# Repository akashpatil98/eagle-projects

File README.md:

# eagle-projects
 This repository contains all of my Eagle CAD PCB design projects.
# Pico
The Gerber files and BoM for Pico can be found [here](https://github.com/akashpatil98/eagle-projects/tree/main/Pico).
Pico is based on Atmel ATSAMD21 microcontroller. It can be programmed using Adruino IDE or Adafruit's CircuitPython.
It has an ARM Cortex M0+ core with a maximum clock speed of 48 MHz.

# Raven BLE
Raven BLE board is based on Nordic Semiconductor's nRF52840 SoC and supports BLE 5.0. It has an ARM Cortex M4F core and supports upto 64 MHz clock speed.
The gerber files for Ravel BLE can be found [here](https://github.com/akashpatil98/eagle-projects/tree/main/Raven_BLE).

# Software
The PCBs listed here are designed using AutoDesk EAGLE software (version 9.5.2).

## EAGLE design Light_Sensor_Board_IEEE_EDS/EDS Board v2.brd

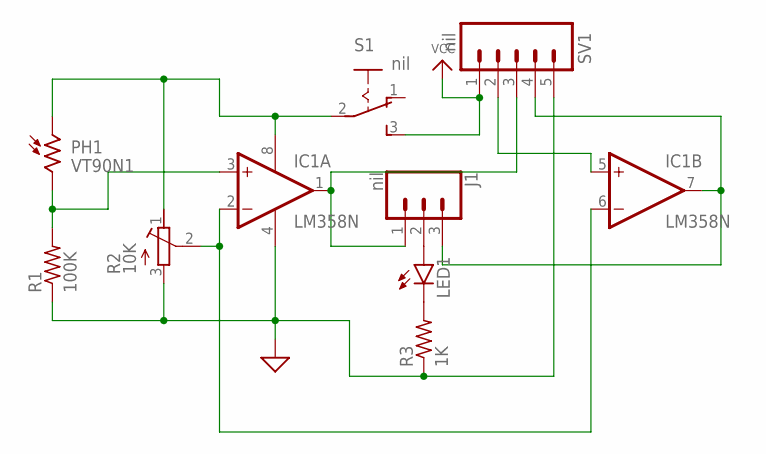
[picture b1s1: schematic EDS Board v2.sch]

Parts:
IC1: LM358N; DIL08
J1: nil; 1X03
LED1: RED; LED5MM
PH1: VT90N1; VT900
R1: 100K; 0207/7
R2: 10K; RTRIMT93YA
R3: 1K; 0207/7
S1: nil; 255SB
SV1: nil; 1X05

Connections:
GND: IC1.4 (V-), R1.1, R2.3 (A), R3.1, SV1.5
unnamed: IC1.2 (-IN), IC1.6 (-IN), R2.2 (S)
unnamed: IC1.3 (+IN), PH1.2, R1.2
unnamed: IC1.1 (OUT), J1.1, SV1.3
unnamed: LED1.K (C), R3.2
unnamed: IC1.7 (OUT), J1.3, SV1.4
unnamed: IC1.5 (+IN), SV1.2
unnamed: IC1.8 (V+), PH1.1, R2.1 (E), S1.2
unnamed: J1.2, LED1.A
VCC: S1.3 (S), SV1.1

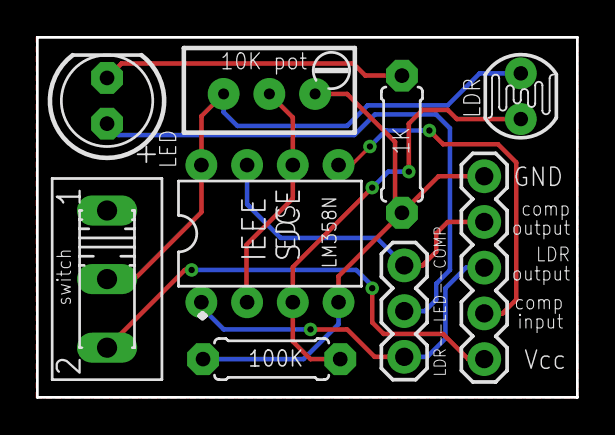
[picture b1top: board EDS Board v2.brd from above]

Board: 2 copper layers, 30.0 x 20.0 mm, 9 parts (0 on the bottom side), 10 nets.

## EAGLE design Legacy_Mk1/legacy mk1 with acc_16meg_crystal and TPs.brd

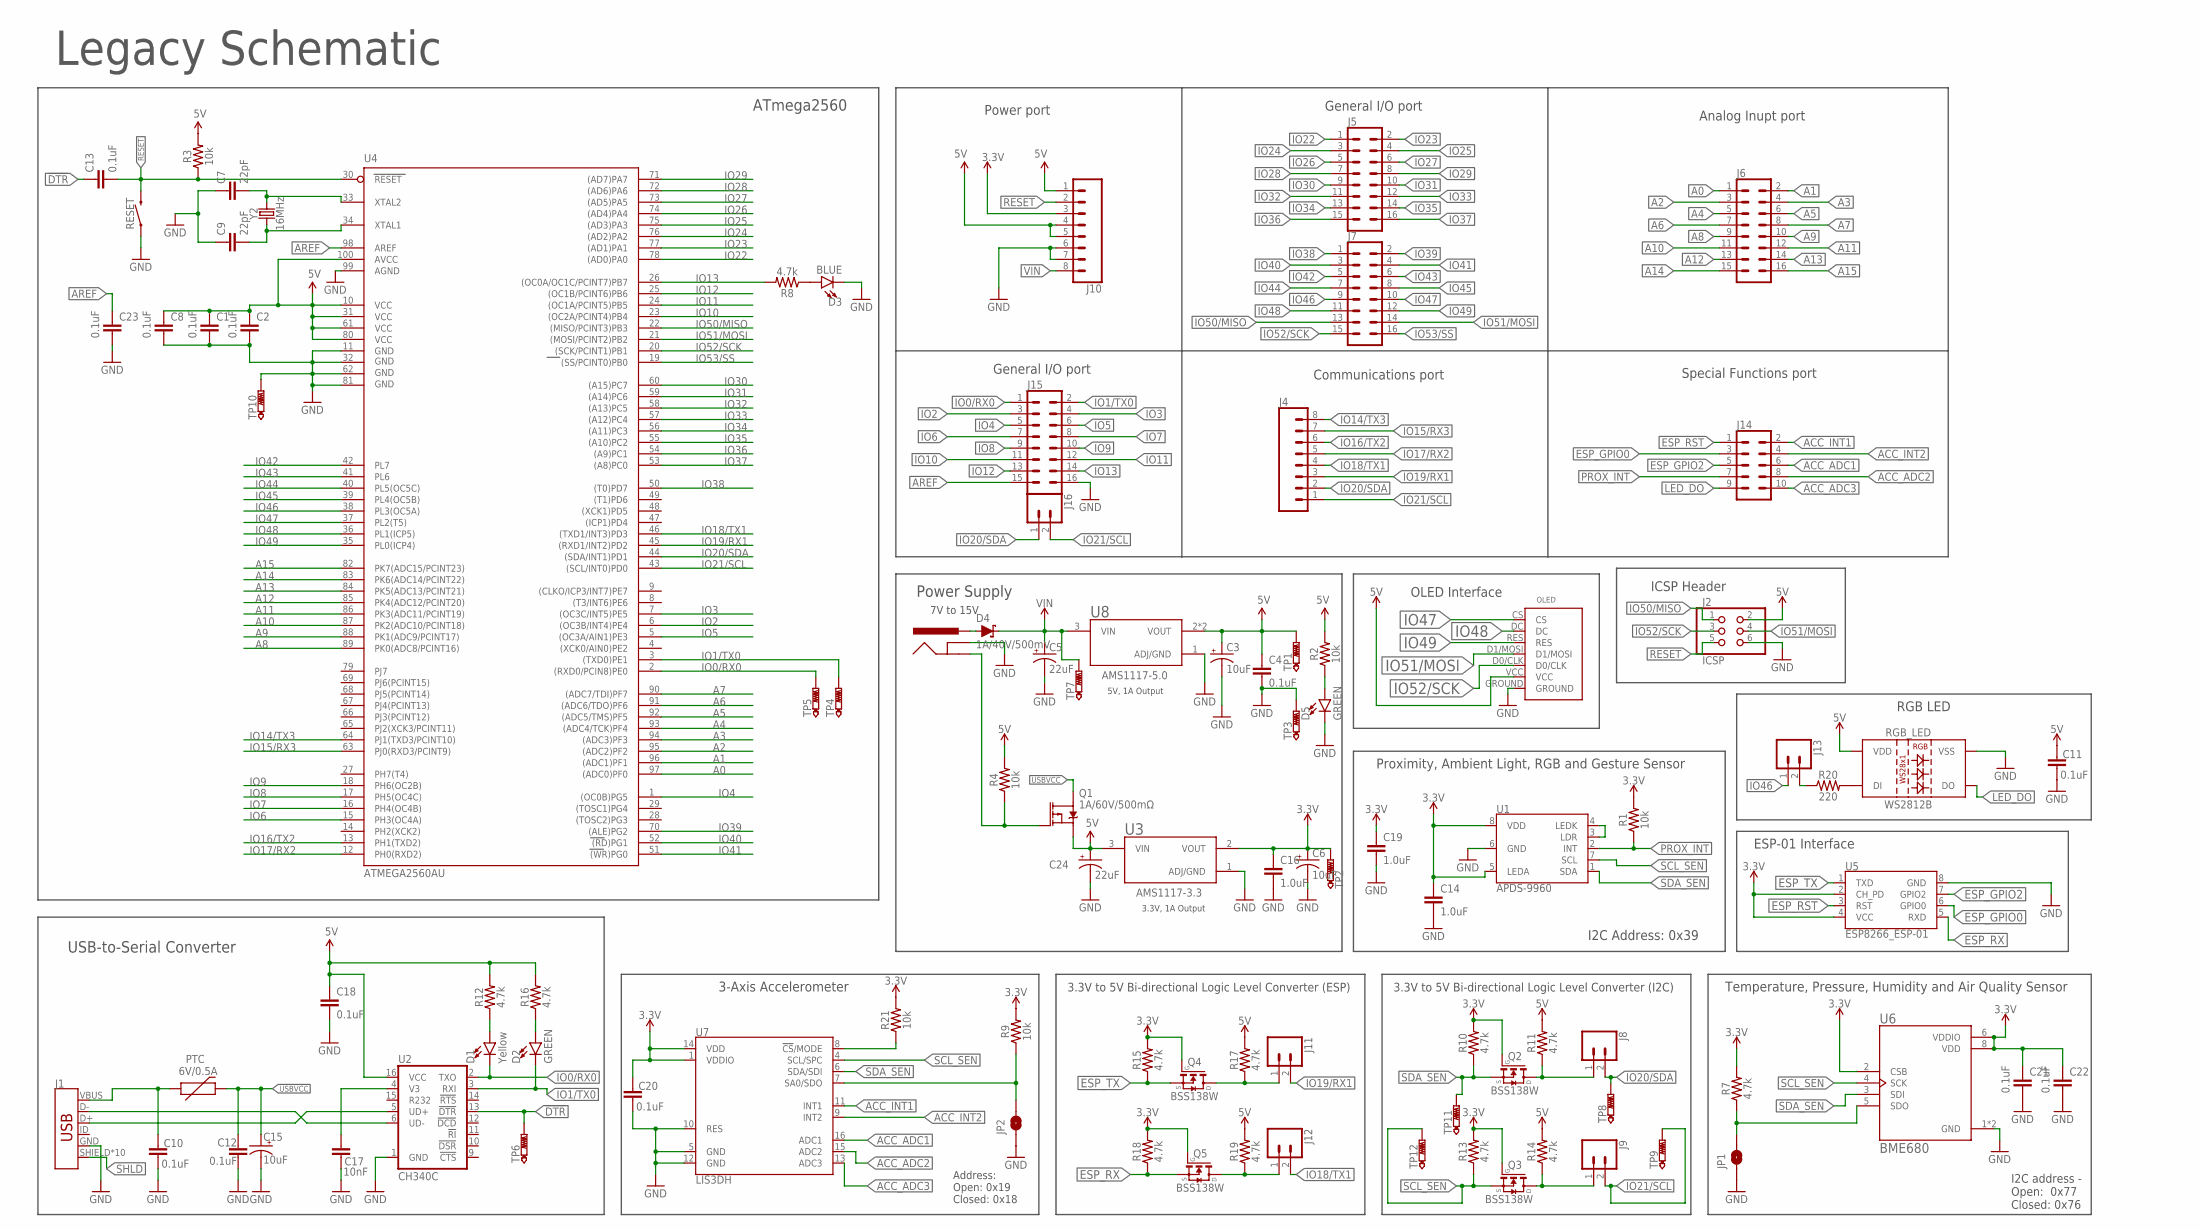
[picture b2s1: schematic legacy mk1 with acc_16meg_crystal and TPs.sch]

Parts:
C1, C2, C4, C8, C10, C11, C12, C13, C18, C20, C21, C22, C23: 0.1uF; 0603
C3, C6, C15: 10uF; EIA3216
C5, C24: 22uF; CT3528
C7, C9: 22pF; 0603
C14, C16, C19: 1.0uF; 0603-CAP
C17: 10nF; 0603-CAP
D1: Yellow; LED-0603
D2, D5: GREEN; LED-0603
D3: BLUE; LED-0603
D4: 1A/40V/500mV; SMA-DIODE
J1: AMP FCI 10103594-0001LF; USB-MICROB-PTH-MILL
J2: ICSP; 2X03
J3: POWER_JACKSLT; POWER_JACK_SLOT
J4, J10: CONN_08"; 1X08
J5, J6, J7, J15: CONN_08X2_HEADER; 2X8
J8, J9, J11, J12, J13, J16: CONN_02; 1X02
J14: CONN_05X2PTH; 2X5
JP1, JP2: JUMPER-SMT_2_NO_SILK; SMT-JUMPER_2_NO_SILK
OLED: OLED_SHIELD
PTC: 6V/0.5A; 1206
Q1: 1A/60V/500mΩ; SOT23-3
Q2, Q3, Q4, Q5: BSS138W; SOT323-R
R1, R2, R3, R4, R9, R21: 10k; 0603
R7, R8, R10, R11, R12, R13, R14, R15, R16, R17, R18, R19: 4.7k; 0603
R20: 220; 0603
RESET: MOMENTARY-SWITCH-SPST-PTH-6.0MM; TACTILE_SWITCH_PTH_6.0MM
RGB_LED: WS2812B
TP1, TP2, TP3, TP4, TP5, TP6, TP7, TP8, TP9, TP10, TP11, TP12: PTR1B1,27; B1,27
U1: APDS-9960
U2: CH340C; SO016
U3: AMS1117-3.3; SOT229P700X180-4N
U4: ATMEGA2560AU; TQFP100
U5: ESP8266_ESP-01
U6: BME680; PSON80P300X300X100-8N
U7: LIS3DH; LGA-16-3X3
U8: AMS1117-5.0; SOT229P700X180-4N
Y2: 16MHz; HC49US

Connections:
3.3V: C6.+, C14.1, C16.1, C19.1, C20.1, C21.1, C22.1, J10.3, Q2.1 (G), Q3.1 (G), Q4.1 (G), Q5.1 (G), R1.2, R7.2, R9.2, R10.2, R13.2, R15.2, R18.2, R21.2, TP2.TP, U1.5 (LEDA), U1.8 (VDD), U3.2 (VOUT), U5.2 (CH_PD), U5.4 (VCC), U6.2 (CSB), U6.6 (VDDIO), U6.8 (VDD), U7.1 (VDDIO), U7.14 (VDD)
5V: C1.1, C2.1, C3.+, C4.1, C8.1, C11.1, C18.1, C24.+, J2.2, J10.1, J10.4, J10.5, OLED.VCC, Q1.2 (S), R2.2, R3.2, R4.2, R11.2, R12.2, R14.2, R16.2, R17.2, R19.2, RGB_LED.1 (VDD), TP1.TP, U2.16 (VCC), U3.3 (VIN), U4.10 (VCC), U4.31 (VCC1), U4.61 (VCC2), U4.80 (VCC3), U4.100 (AVCC), U8.2 (VOUT), U8.4 (VOUT)
!DTR: C13.1, TP6.TP, U2.13 (!DTR)
A0: J6.1, U4.97 ((ADC0)PF0)
A1: J6.2, U4.96 ((ADC1)PF1)
A2: J6.3, U4.95 ((ADC2)PF2)
A3: J6.4, U4.94 ((ADC3)PF3)
A4: J6.5, U4.93 ((ADC4/TCK)PF4)
A5: J6.6, U4.92 ((ADC5/TMS)PF5)
A6: J6.7, U4.91 ((ADC6/TDO)PF6)
A7: J6.8, U4.90 ((ADC7/TDI)PF7)
A8: J6.9, U4.89 (PK0(ADC8/PCINT16))
A9: J6.10, U4.88 (PK1(ADC9/PCINT17))
A10: J6.11, U4.87 (PK2(ADC10/PCINT18))
A11: J6.12, U4.86 (PK3(ADC11/PCINT19))
A12: J6.13, U4.85 (PK4(ADC12/PCINT20))
A13: J6.14, U4.84 (PK5(ADC13/PCINT21))
A14: J6.15, U4.83 (PK6(ADC14/PCINT22))
A15: J6.16, U4.82 (PK7(ADC15/PCINT23))
ACC_ADC1: J14.6, U7.16 (ADC1)
ACC_ADC2: J14.8, U7.15 (ADC2)
ACC_ADC3: J14.10, U7.13 (ADC3)
ACC_INT1: J14.2, U7.11 (INT1)
ACC_INT2: J14.4, U7.9 (INT2)
AREF: C23.1, J15.15, U4.98 (AREF)
ESP_GPIO0: J14.3, U5.6 (GPIO0)
ESP_GPIO2: J14.5, U5.7 (GPIO2)
ESP_RST: J14.1, U5.3 (RST)
ESP_RX: Q5.2 (S), R18.1, U5.5 (RXD)
ESP_TX: Q4.2 (S), R15.1, U5.1 (TXD)
GND: C1.2, C2.2, C3.-, C4.2, C5.-, C6.-, C7.1, C8.2, C9.1, C10.2, C11.2, C12.2, C14.2, C15.-, C16.2, C17.2, C18.2, C19.2, C20.2, C21.2, C22.2, C23.2, C24.-, D3.C, D5.C, J1.GND, J2.6, J3.GND@1 (GNDBREAK), J10.6, J10.7, J15.16, JP1.1, JP2.1, OLED.GROUND, RESET.1, RGB_LED.3 (VSS), TP3.TP, TP10.TP, U1.6 (GND), U2.1 (GND), U3.1 (ADJ/GND), U4.11 (GND), U4.32 (GND1), U4.62 (GND2), U4.81 (GND3), U4.99 (AGND), U5.8 (GND), U6.1 (GND), U6.7 (GND), U7.5 (GND), U7.10 (RES), U7.12 (GND), U8.1 (ADJ/GND)
INSERT: J3.GND@2 (GND), Q1.1 (G), R4.1
IO0/RX0: D1.C, J15.1, TP5.TP, U2.2 (TXO), U4.2 ((RXD0/PCIN8)PE0)
IO1/TX0: D2.C, J15.2, TP4.TP, U2.3 (RXI), U4.3 ((TXD0)PE1)
IO2: J15.3, U4.6 ((OC3B/INT4)PE4)
IO3: J15.4, U4.7 ((OC3C/INT5)PE5)
IO4: J15.5, U4.1 ((OC0B)PG5)
IO5: J15.6, U4.5 ((OC3A/AIN1)PE3)
IO6: J15.7, U4.15 (PH3(OC4A))
IO7: J15.8, U4.16 (PH4(OC4B))
IO8: J15.9, U4.17 (PH5(OC4C))
IO9: J15.10, U4.18 (PH6(OC2B))
IO10: J15.11, U4.23 ((OC2A/PCINT4)PB4)
IO11: J15.12, U4.24 ((OC1A/PCINT5)PB5)
IO12: J15.13, U4.25 ((OC1B/PCINT6)PB6)
IO13: J15.14, R8.2, U4.26 ((OC0A/OC1C/PCINT7)PB7)
IO14/TX3: J4.8, U4.64 (PJ1(TXD3/PCINT10))
IO15/RX3: J4.7, U4.63 (PJ0(RXD3/PCINT9))
IO16/TX2: J4.6, U4.13 (PH1(TXD2))
IO17/RX2: J4.5, U4.12 (PH0(RXD2))
IO18/TX1: J4.4, J12.2, U4.46 ((TXD1/INT3)PD3)
IO19/RX1: J4.3, J11.2, U4.45 ((RXD1/INT2)PD2)
IO20/SDA: J4.2, J8.2, J16.1, TP8.TP, U4.44 ((SDA/INT1)PD1)
IO21/SCL: J4.1, J9.2, J16.2, TP9.TP, U4.43 ((SCL/INT0)PD0)
IO22: J5.1, U4.78 ((AD0)PA0)
IO23: J5.2, U4.77 ((AD1)PA1)
IO24: J5.3, U4.76 ((AD2)PA2)
IO25: J5.4, U4.75 ((AD3)PA3)
IO26: J5.5, U4.74 ((AD4)PA4)
IO27: J5.6, U4.73 ((AD5)PA5)
IO28: J5.7, U4.72 ((AD6)PA6)
IO29: J5.8, U4.71 ((AD7)PA7)
IO30: J5.9, U4.60 ((A15)PC7)
IO31: J5.10, U4.59 ((A14)PC6)
IO32: J5.11, U4.58 ((A13)PC5)
IO33: J5.12, U4.57 ((A12)PC4)
IO34: J5.13, U4.56 ((A11)PC3)
IO35: J5.14, U4.55 ((A10)PC2)
IO36: J5.15, U4.54 ((A9)PC1)
IO37: J5.16, U4.53 ((A8)PC0)
IO38: J7.1, U4.50 ((T0)PD7)
IO39: J7.2, U4.70 ((ALE)PG2)
IO40: J7.3, U4.52 ((RD)PG1)
IO41: J7.4, U4.51 ((WR)PG0)
IO42: J7.5, U4.42 (PL7)
IO43: J7.6, U4.41 (PL6)
IO44: J7.7, U4.40 (PL5(OC5C))
IO45: J7.8, U4.39 (PL4(OC5B))
IO46: J7.9, J13.1, U4.38 (PL3(OC5A))
IO47: J7.10, OLED.CS, U4.37 (PL2(T5))
IO48: J7.11, OLED.DC, U4.36 (PL1(ICP5))
IO49: J7.12, OLED.RES, U4.35 (PL0(ICP4))
IO50/MISO: J2.1, J7.13, U4.22 ((MISO/PCINT3)PB3)
IO51/MOSI: J2.4, J7.14, OLED.D1/MOSI, U4.21 ((MOSI/PCINT2)PB2)
IO52/SCK: J2.3, J7.15, OLED.D0/CLK, U4.20 ((SCK/PCINT1)PB1)
IO53/SS: J7.16, U4.19 ((SS/PCINT0)PB0)
LED_DO: J14.9, RGB_LED.2 (DO)
unnamed: C7.2, U4.33 (XTAL2), Y2.2
unnamed: D5.A, R2.1
unnamed: C9.2, U4.34 (XTAL1), Y2.1
unnamed: JP1.2, R7.1, U6.5 (SDO)
unnamed: D2.A, R16.1
unnamed: C17.1, U2.4 (V3)
unnamed: U1.3 (LDR), U1.4 (LEDK)
unnamed: D3.A, R8.1
unnamed: D1.A, R12.1
unnamed: JP2.2, R9.1, U7.7 (SA0/SDO)
unnamed: J13.2, R20.1
unnamed: J8.1, Q2.3 (D), R11.1
unnamed: J1.D-, U2.6 (UD-)
unnamed: J1.D+, U2.5 (UD+)
unnamed: J11.1, Q4.3 (D), R17.1
unnamed: J9.1, Q3.3 (D), R14.1
unnamed: R21.1, U7.8 (!CS!/MODE)
unnamed: R20.2, RGB_LED.4 (DI)
unnamed: J12.1, Q5.3 (D), R19.1
PROX_INT: J14.7, R1.1, U1.2 (INT)
PWRIN: D4.A, J3.PWR
RESET: C13.2, J2.5, J10.2, R3.1, RESET.3 (2), U4.30 (RESET)
SCL_SEN: Q3.2 (S), R13.1, TP12.TP, U1.7 (SCL), U6.4 (SCK), U7.4 (SCL/SPC)
SDA_SEN: Q2.2 (S), R10.1, TP11.TP, U1.1 (SDA), U6.3 (SDI), U7.6 (SDA/SDI)
SHLD: J1.SHIELD, J1.SHIELD2 (SHIELD), J1.SHIELD3 (SHIELD), J1.SHIELD4 (SHIELD), J1.SHIELD5 (SHIELD), J1.SHIELD6 (SHIELD), J1.SHIELD7 (SHIELD), J1.SHIELD8 (SHIELD), J1.SHIELD9 (SHIELD), J1.SHIELD10 (SHIELD)
USBVCC: C12.1, C15.+, PTC.2, Q1.3 (D)
VIN: C5.+, D4.C, J10.8, TP7.TP, U8.3 (VIN)
VUSB: C10.1, J1.VBUS, PTC.1

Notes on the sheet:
USB-to-Serial Converter
Power Supply
3-Axis Accelerometer
3.3V to 5V Bi-directional Logic Level Converter (I2C)
3.3V to 5V Bi-directional Logic Level Converter (ESP)
RGB LED
Address: Open: 0x19 Closed: 0x18
7V to 15V
ESP-01 Interface
ICSP Header
Proximity, Ambient Light, RGB and Gesture Sensor
I2C Address: 0x39
Temperature, Pressure, Humidity and Air Quality Sensor
I2C address - Open: 0x77 Closed: 0x76
Power port
Communications port
Special Functions port
Analog Inupt port
General I/O port
ATmega2560
OLED Interface
Legacy Schematic
5V, 1A Output
3.3V, 1A Output

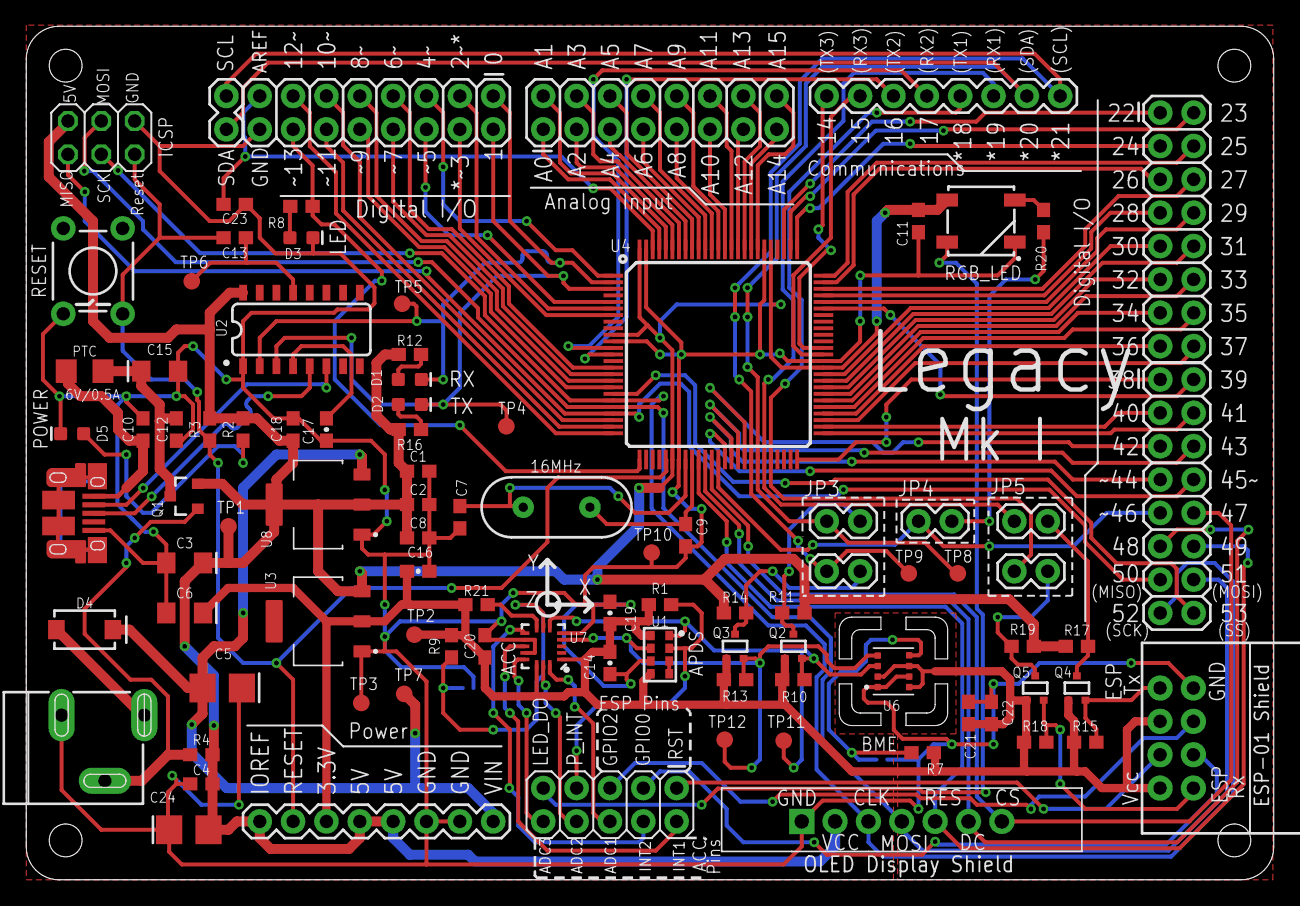
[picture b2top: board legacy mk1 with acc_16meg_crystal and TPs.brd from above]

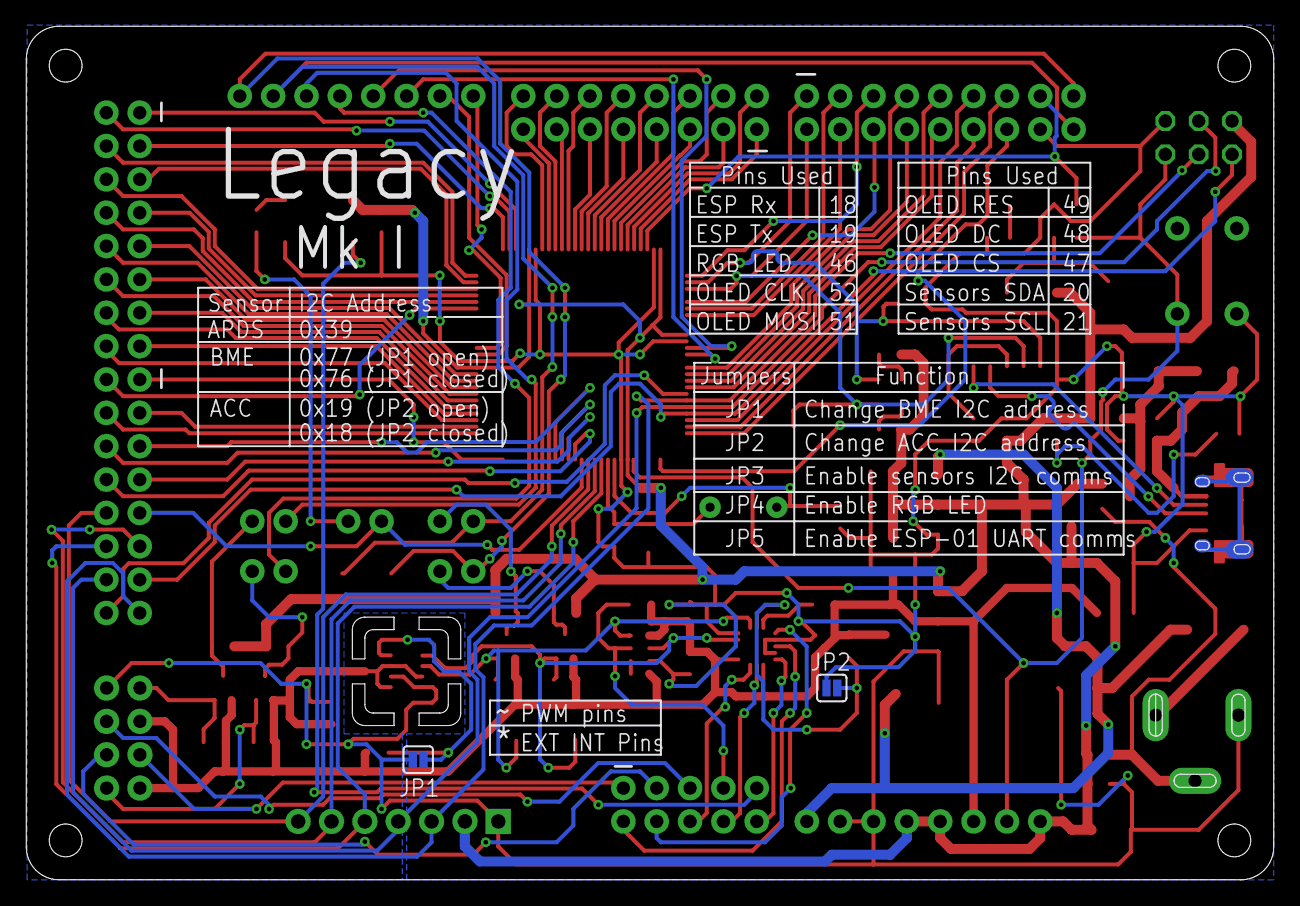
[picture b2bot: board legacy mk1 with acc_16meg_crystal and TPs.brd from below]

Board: 2 copper layers, 95.0 x 65.0 mm, 96 parts (2 on the bottom side), 115 nets.

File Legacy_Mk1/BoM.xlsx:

Qty | Value | Device | Package | Parts | Description
6 |  | CONN_02 | 1X02 | J8, J9, J11, J12, J13, J16 | Multi connection point. Often used as Generic Header-pin footprint for 0.1 inch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
1 |  | CONN_05X2PTH | 2X5 | J14 | Multi connection point. Often used as Generic Header-pin footprint for 0.1 inch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
2 |  | CONN_08";1X08" | J4, J10 | J4, J10 | Multi connection point. Often used as Generic Header-pin footprint for 0.1 inch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
4 |  | CONN_08X2_HEADER | 2X8 | J5, J6, J7, J15 | Multi connection point. Often used as Generic Header-pin footprint for 0.1 inch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
13 | 0.1uF | 0.1UF-0603-25V-(+80/-20%) | 0603 | C1, C2, C4, C8, C10, C11, C12, C13, C18, C20, C21, C22, C23 | 0.1ÂµF ceramic capacitors
3 | 1.0uF | 1.0UF-16V-10%(0603) | 0603-CAP | C14, C16, C19 | CAP-00868
6 | 10k | 10KOHM-0603-1/10W-1% | 0603 | R1, R2, R3, R4, R9, R21 | 10kÎ© resistor
1 | 10nF | 10NF/10000PF-50V-10%(0603) | 0603-CAP | C17 | CAP-00867
3 | 10uF | 10UF-POLAR-EIA3216-16V-10%(TANT) | EIA3216 | C3, C6, C15 | 10.0ÂµF polarized capacitors
1 | 16MHz | CRYSTAL-16MHZPTH-HC49US | HC49US | Y2 | 16MHz Crystal
1 | 1A/40V/500mV | DIODE-SCHOTTKY-SS14 | SMA-DIODE | D4 | Schottky diode
1 | 1A/60V/500mÎ© | MOSFET-PCH-ZXMP6A13F | SOT23-3 | Q1 | P-channel MOSFETs
1 | 220 | 220OHM-0603-1/10W-1% | 0603 | R20 | 220Î© resistor
2 | 22pF | 22PF-0603-50V-5% | 0603 | C7, C9 | 22pF ceramic capacitors
2 | 22uF | CPOL-USCT3528 | CT3528 | C5, C24 | POLARIZED CAPACITOR, American symbol
12 | 4.7k | 4.7KOHM-0603-1/10W-1% | 0603 | R7, R8, R10, R11, R12, R13, R14, R15, R16, R17, R18, R19 | 4.7kÎ© resistor
1 | 6V/0.5A | PPTC_6V500MA-2 | 1206 | PTC | Resettable Fuse PPTC
1 | AMP FCI 10103594-0001LF | USB_MICRO-B_HALF_PTH_MILL | USB-MICROB-PTH-MILL | J1 | USB Type Micro-B Connector
1 | AMS1117-3.3 | AMS1117-3.3 | SOT229P700X180-4N | U3 | Sot223/Pkg 1-Amp 3.3-Volt Low Drop Out Voltage Regulatator
1 | AMS1117-5.0 | AMS1117-5.0 | SOT229P700X180-4N | U8 | Sot223/Pkg 1-Amp 5-Volt Low Drop Out Voltage Regulatator
1 | APDS-9960 | APDS-9960 | APDS-9960 | U1 | Avago APDS-9960 Digital Proximity, Ambient Light, RGB, and Gesture Sensor.
1 | ATMEGA2560AU | ATMEGA2560AU | TQFP100 | U4 | Atmel 100-pin 8-bit uC
1 | BLUE | LED-BLUE0603 | LED-0603 | D3 | Blue SMD LED
1 | BME680 | BME680 | PSON80P300X300X100-8N | U6 | Integrated Environmental Unit
4 | BSS138W | BSS138W | SOT323-R | Q2, Q3, Q4, Q5 | N-Channel MOSFET
1 | CH340C | CH340C | SO016 | U2
1 | ESP8266_ESP-01 | ESP8266_ESP-01 | ESP8266_ESP-01 | U5 | ESP8266 ESP-01 Module
2 | GREEN | LED-GREEN0603 | LED-0603 | D2, D5 | Green SMD LED
1 | ICSP | PINHD-2X3 | 2X03 | J2 | PIN HEADER
2 | JUMPER-SMT_2_NO_SILK | JUMPER-SMT_2_NO_SILK | SMT-JUMPER_2_NO_SILK | JP1, JP2 | Normally open jumper
1 | LIS3DH | LIS3DH | LGA-16-3X3 | U7 | ST Microelectronics LIS3DH 3-Axis +/-2/4/8/16g SPI/I2C Accelerometer
1 | MOMENTARY-SWITCH-SPST-PTH-6.0MM | MOMENTARY-SWITCH-SPST-PTH-6.0MM | TACTILE_SWITCH_PTH_6.0MM | RESET | Momentary Switch (Pushbutton) - SPST
1 | OLED_SHIELD | OLED_SHIELD | OLED_SHIELD | OLED | This is an OLED display shield for 0.96 OLED display module (SSD1306)."
1 | POWER_JACKSLT | POWER_JACKSLT | POWER_JACK_SLOT | J3 | Power Jack Connector
1 | WS2812B | WS2812B | WS2812B | RGB_LED | WS2812B SMD addressable RGB LED
1 | Yellow | LED-YELLOW0603 | LED-0603 | D1 | Yellow SMD LED

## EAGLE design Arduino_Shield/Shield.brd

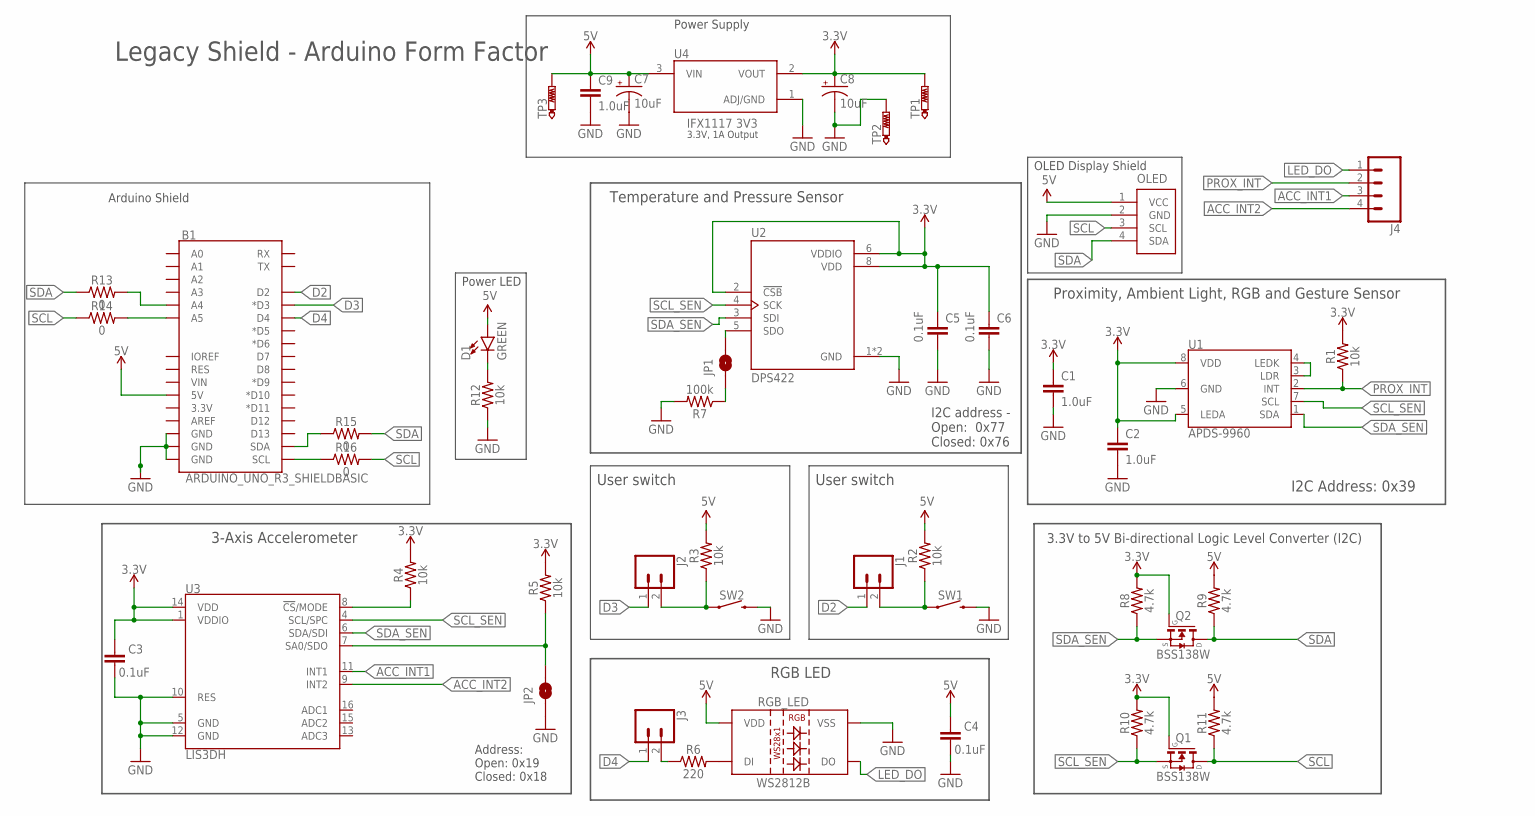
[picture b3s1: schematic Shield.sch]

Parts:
B1: ARDUINO_UNO_R3_SHIELDBASIC; UNO_R3_SHIELD
C1, C2, C9: 1.0uF; 0603-CAP
C3, C4, C5, C6: 0.1uF; 0603
C7, C8: 10uF; EIA3528
D1: GREEN; LED-1206
J1, J2, J3: CONN_02; 1X02
J4: CONN_04; 1X04
JP1, JP2: JUMPER-SMT_2_NO_SILK; SMT-JUMPER_2_NO_SILK
OLED: OLED_4_PIN; OLED_4PIN
Q1, Q2: BSS138W; SOT323-R; DIGI-KEY_PART_NUMBER BSS138WH6327XTSA1CT-ND
R1, R2, R3, R4, R5, R12: 10k; 0603
R6: 220; 0603
R7: 100k; 0603
R8, R9, R10, R11: 4.7k; 0603
R13, R14, R15, R16: 0; 0603
RGB_LED: WS2812B
SW1, SW2: MOMENTARY-SWITCH-SPST-PTH-6.0MM; TACTILE_SWITCH_PTH_6.0MM
TP1, TP2, TP3: PTR1TP08R; TP08R
U1: APDS-9960; DIGI-KEY_PART_NUMBER 516-3480-1-ND
U2: DPS422; XDCR_DPS422; DIGI-KEY_PART_NUMBER DPS422XTSA1CT-ND
U3: LIS3DH; LGA-16-3X3
U4: IFX1117 3V3; SOT229P700X180-4N; DIGI-KEY_PART_NUMBER IFX1117MEV33HTMA1CT-ND

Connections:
3.3V: C1.1, C2.1, C3.1, C5.1, C6.1, C8.A (+), Q1.1 (G), Q2.1 (G), R1.2, R4.2, R5.2, R8.2, R10.2, TP1.TP, U1.5 (LEDA), U1.8 (VDD), U2.2 (!CSB), U2.6 (VDDIO), U2.8 (VDD), U3.1 (VDDIO), U3.14 (VDD), U4.2 (VOUT)
5V: B1.5V, C4.1, C7.A (+), C9.1, D1.A, OLED.1 (VCC), R2.2, R3.2, R9.2, R11.2, RGB_LED.1 (VDD), TP3.TP, U4.3 (VIN)
ACC_INT1: J4.3, U3.11 (INT1)
ACC_INT2: J4.4, U3.9 (INT2)
D2: B1.D2, J1.1
D3: B1.D3 (*D3), J2.1
D4: B1.D4, J3.1
GND: B1.GND@0 (GND), B1.GND@1 (GND), B1.GND@2 (GND), C1.2, C2.2, C3.2, C4.2, C5.2, C6.2, C7.C (-), C8.C (-), C9.2, JP2.1, OLED.2 (GND), R7.2, R12.1, RGB_LED.3 (VSS), SW1.3 (2), SW2.3 (2), TP2.TP, U1.6 (GND), U2.1 (GND), U2.7 (GND), U3.5 (GND), U3.10 (RES), U3.12 (GND), U4.1 (ADJ/GND)
LED_DO: J4.1, RGB_LED.2 (DO)
unnamed: J1.2, R2.1, SW1.1
unnamed: J2.2, R3.1, SW2.1
unnamed: D1.C, R12.2
unnamed: JP1.2, U2.5 (SDO)
unnamed: JP1.1, R7.1
unnamed: B1.A4, R13.2
unnamed: U1.3 (LDR), U1.4 (LEDK)
unnamed: B1.A5, R14.2
unnamed: B1.SDA, R15.1
unnamed: JP2.2, R5.1, U3.7 (SA0/SDO)
unnamed: J3.2, R6.1
unnamed: B1.SCL, R16.1
unnamed: R4.1, U3.8 (!CS!/MODE)
unnamed: R6.2, RGB_LED.4 (DI)
PROX_INT: J4.2, R1.1, U1.2 (INT)
SCL: OLED.3 (SCL), Q1.3 (D), R11.1, R14.1, R16.2
SCL_SEN: Q1.2 (S), R10.1, U1.7 (SCL), U2.4 (SCK), U3.4 (SCL/SPC)
SDA: OLED.4 (SDA), Q2.3 (D), R9.1, R13.1, R15.2
SDA_SEN: Q2.2 (S), R8.1, U1.1 (SDA), U2.3 (SDI), U3.6 (SDA/SDI)

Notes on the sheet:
3-Axis Accelerometer
Address: Open: 0x19 Closed: 0x18
3.3V to 5V Bi-directional Logic Level Converter (I2C)
Temperature and Pressure Sensor
I2C address - Open: 0x77 Closed: 0x76
Proximity, Ambient Light, RGB and Gesture Sensor
I2C Address: 0x39
RGB LED
User switch
Power LED
3.3V, 1A Output
Power Supply
OLED Display Shield
Arduino Shield
Legacy Shield - Arduino Form Factor

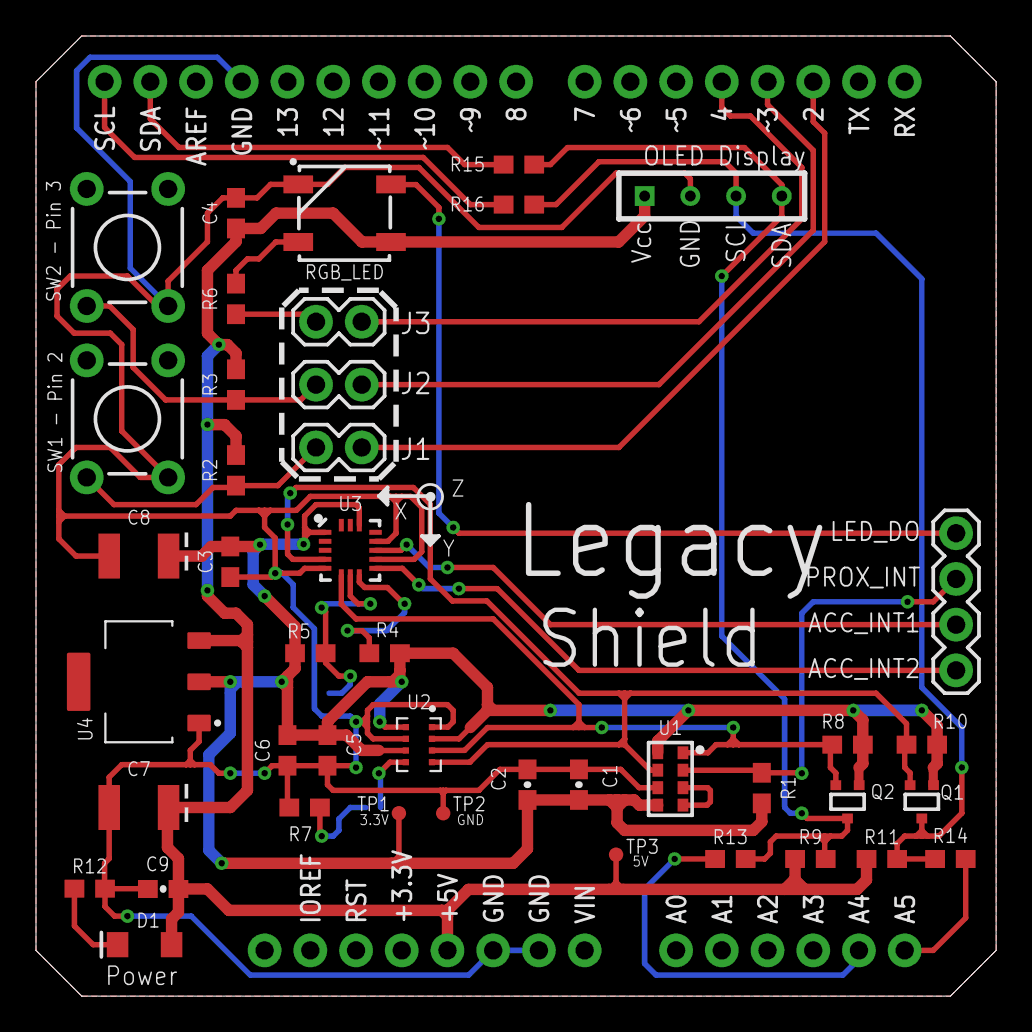
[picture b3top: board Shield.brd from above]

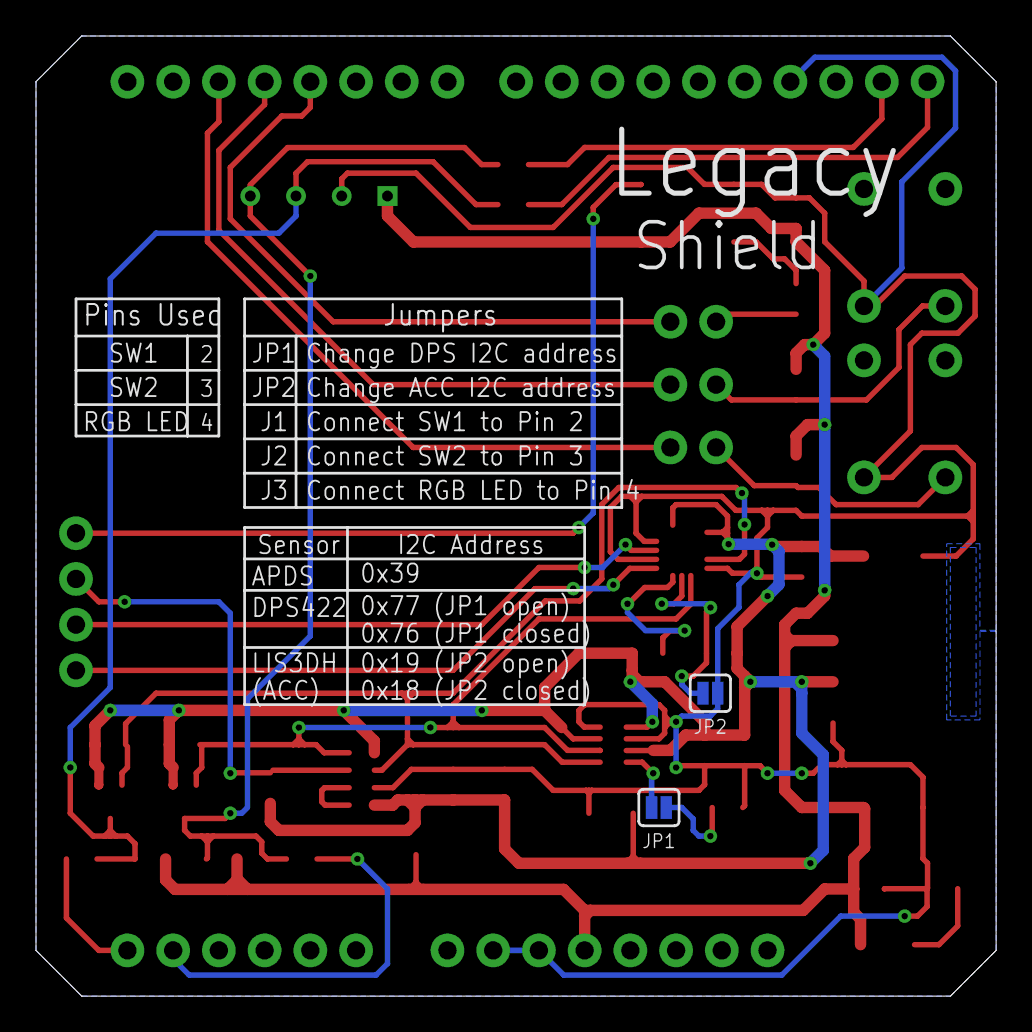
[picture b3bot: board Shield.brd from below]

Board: 2 copper layers, 53.3 x 53.3 mm, 46 parts (2 on the bottom side), 28 nets.

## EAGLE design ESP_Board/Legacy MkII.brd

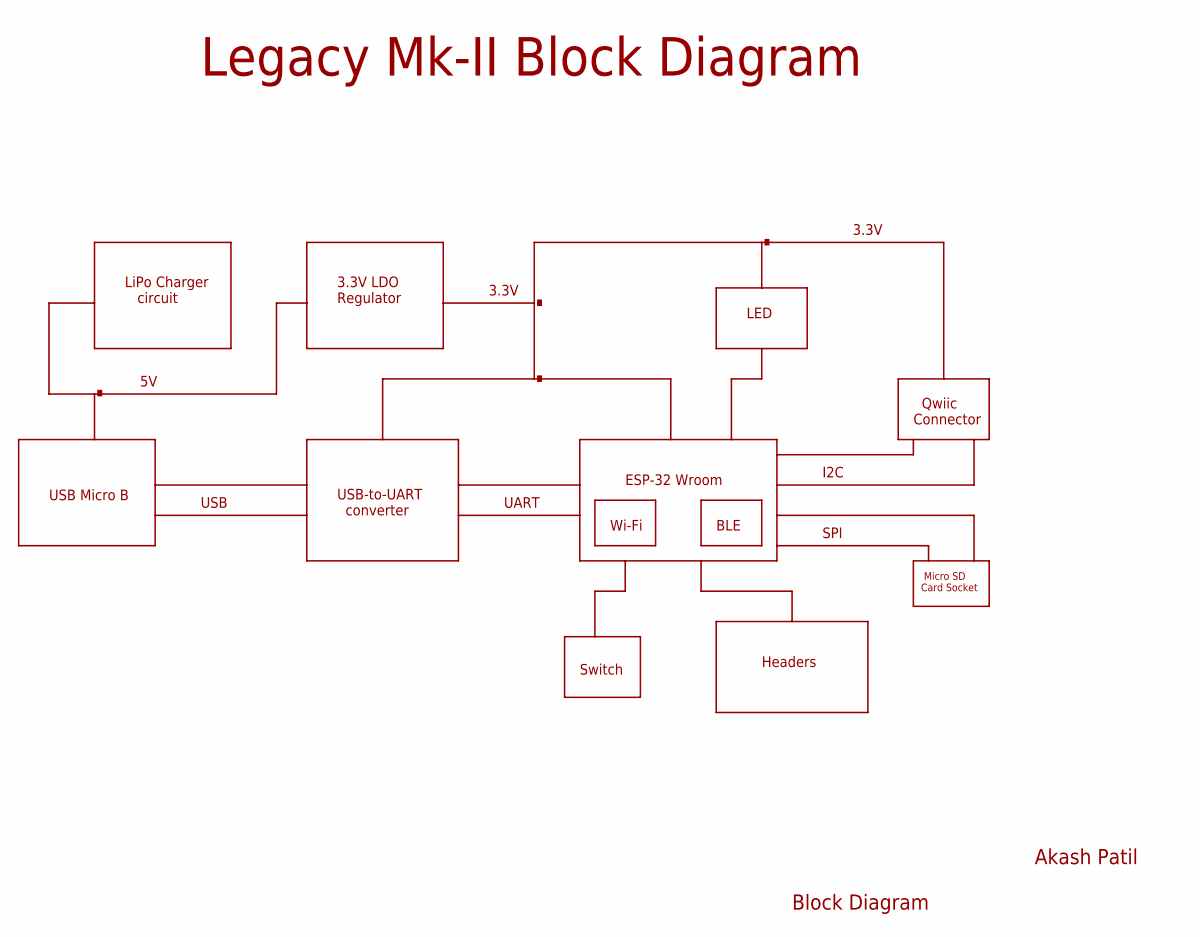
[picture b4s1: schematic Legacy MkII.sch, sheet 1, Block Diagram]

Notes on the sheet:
Akash Patil
Block Diagram
USB Micro B
USB-to-UART converter
3.3V LDO Regulator
LiPo Charger circuit
ESP-32 Wroom
Wi-Fi
BLE
LED
Switch
Qwiic Connector
3.3V
USB
UART
I2C
Headers
Legacy Mk-II Block Diagram
Micro SD Card Socket
SPI

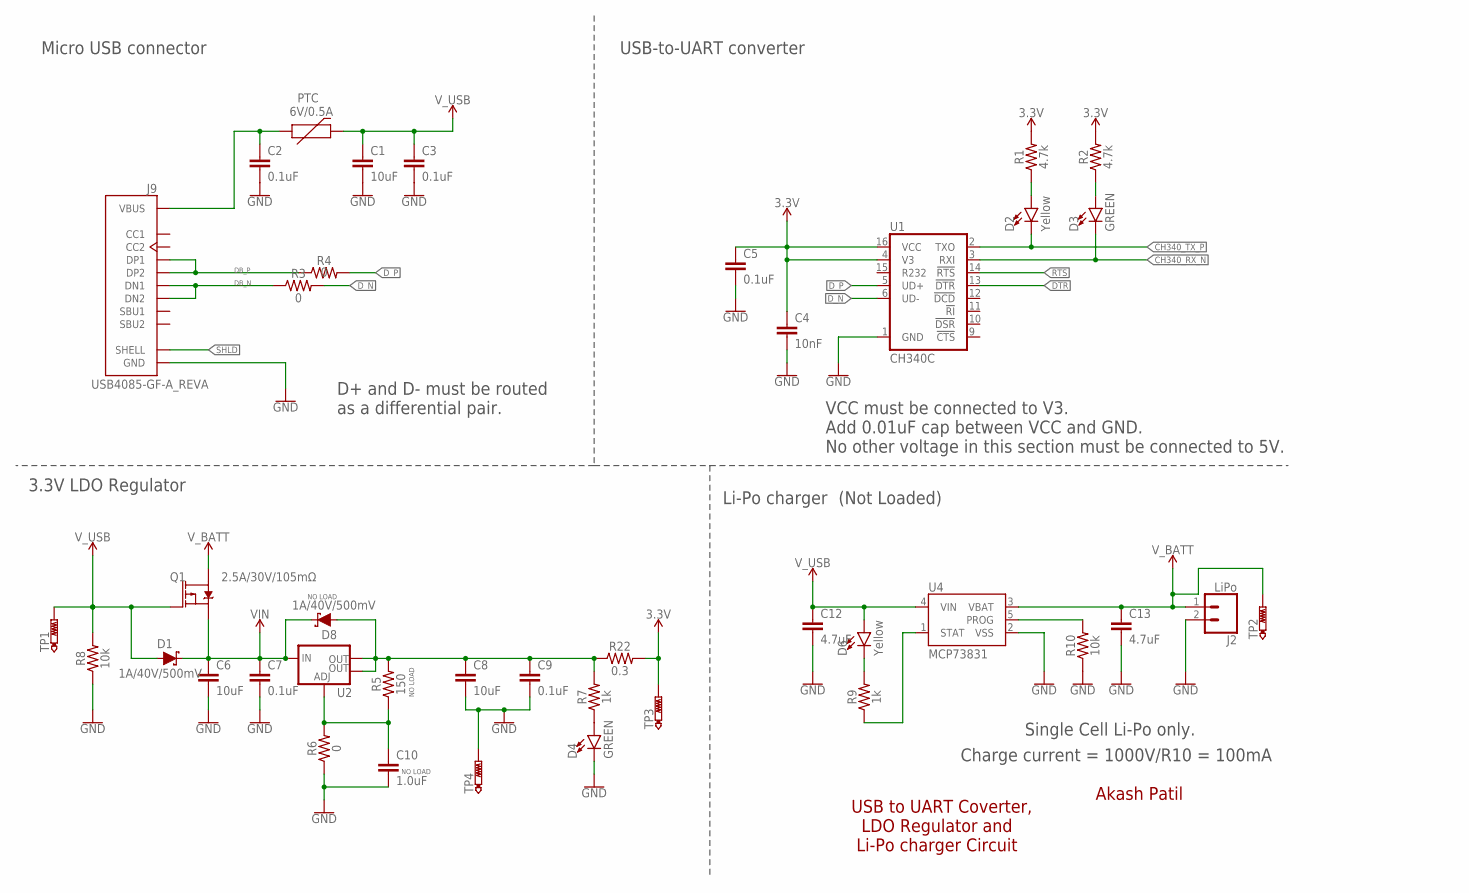
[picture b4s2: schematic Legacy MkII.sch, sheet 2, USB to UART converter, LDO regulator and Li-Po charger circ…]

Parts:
C1, C6, C8: 10uF; 1210
C2, C3, C5, C7, C9: 0.1uF; 0603
C4: 10nF; 0603
C10: 1.0uF; 0603
C12, C13: 4.7uF; 1206
D1, D8: 1A/40V/500mV; SMA-DIODE
D2, D6: Yellow; LED-0603
D3, D4: GREEN; LED-0603
J2: LiPo; JST-2-PTH-NS
J9: USB4085-GF-A_REVA; GCT_USB4085-GF-A_REVA
PTC: 6V/0.5A; 1206
Q1: 2.5A/30V/105mΩ; SOT23-3
R1, R2: 4.7k; 0603
R3, R4, R6: 0; 0603
R5: 150; 0603
R7, R9: 1k; 0603
R8, R10: 10k; 0603
R22: 0.3; 0805
TP1, TP2, TP3, TP4: PTR1B1,27; B1,27
U1: CH340C; SO016
U2: V_REG_LM1117SOT223; SOT223
U4: MCP73831; SOT23-5

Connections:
3.3V: C4.1, C5.1, R1.2, R2.2, R22.2, TP3.TP, U1.4 (V3), U1.16 (VCC); also elsewhere on the board
CH340_RX_N: D3.C, U1.3 (RXI); also elsewhere on the board
CH340_TX_P: D2.C, U1.2 (TXO); also elsewhere on the board
DB_N: J9.A7 (DN1), J9.B7 (DN2), R3.1
DB_P: J9.A6 (DP1), J9.B6 (DP2), R4.1
DTR: U1.13 (!DTR); also elsewhere on the board
D_N: R3.2, U1.6 (UD-)
D_P: R4.2, U1.5 (UD+)
GND: C1.2, C2.2, C3.2, C4.2, C5.2, C6.2, C7.2, C8.2, C9.2, C10.2, C12.2, C13.2, D4.C, J2.2, J9.A1 (GND), J9.A12 (GND), J9.B1 (GND), J9.B12 (GND), R6.1, R8.1, R10.1, TP4.TP, U1.1 (GND), U4.2 (VSS); also elsewhere on the board
unnamed: C2.1, J9.A4 (VBUS), J9.A9 (VBUS), J9.B4 (VBUS), J9.B9 (VBUS), PTC.1
unnamed: D4.A, R7.1
unnamed: C8.1, C9.1, D8.A, R5.2, R7.2, R22.1, U2.2 (OUT), U2.4 (OUT)
unnamed: D2.A, R1.1
unnamed: D3.A, R2.1
unnamed: C10.1, R5.1, R6.2, U2.1 (ADJ)
unnamed: D6.C, R9.2
unnamed: R9.1, U4.1 (STAT)
unnamed: R10.2, U4.5 (PROG)
RTS: U1.14 (!RTS); also elsewhere on the board
SHLD: J9.P1 (SHELL), J9.P2 (SHELL), J9.P3 (SHELL), J9.P4 (SHELL)
VIN: C6.1, C7.1, D1.C, D8.C, Q1.2 (S), U2.3 (IN); also elsewhere on the board
V_BATT: C13.1, J2.1, Q1.3 (D), TP2.TP, U4.3 (VBAT)
V_USB: C1.1, C3.1, C12.1, D1.A, D6.A, PTC.2, Q1.1 (G), R8.2, TP1.TP, U4.4 (VIN); also elsewhere on the board

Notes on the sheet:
VCC must be connected to V3. Add 0.01uF cap between VCC and GND. No other voltage in this section must be connected to 5V.
Akash Patil
USB to UART Coverter, LDO Regulator and Li-Po charger Circuit
D+ and D- must be routed as a differential pair.
Micro USB connector
USB-to-UART converter
Li-Po charger
3.3V LDO Regulator
Single Cell Li-Po only.
Charge current = 1000V/R10 = 100mA
(Not Loaded)

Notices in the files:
parts and their libraries:
SparkFun-Capacitors: Licensing: CC v3.0 Share-Alike You are welcome to use this library for commercial purposes.
SparkFun-Capacitors: Licensing: Creative Commons ShareAlike 4.0 International - https://creativecommons.org/licenses/by-sa/4.0
